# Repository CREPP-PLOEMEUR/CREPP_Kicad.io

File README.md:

# Organisation de la bibliothèque

# Installation d'une bibliothèque via le PCM de KiCad

Ce tutoriel explique comment installer une bibliothèque à partir d'un fichier JSON via le Plugin and Content Manager (PCM) de KiCad.

## Pré-requis

- Avoir installé **KiCad 8** ou une version compatible avec le PCM.
- Disposer de l'adresse du fichier JSON de la bibliothèque :  
  `https://raw.githubusercontent.com/CREPP-PLOEMEUR/CREPP_Kicad.io/refs/heads/main/repository.json`

---

## Étape 1 : Ouvrir le Plugin and Content Manager (PCM)

1. Lancez **KiCad**.
2. Dans le menu principal, cliquez sur **Preferences** > **Manage Plugins**.

---

## Étape 2 : Ajouter un dépôt personnalisé

1. Dans la fenêtre du PCM, cliquez sur l'onglet **Gérer**.

2. Cliquez sur le bouton **Add** pour ajouter un nouveau dépôt.

---

## Étape 3 : Saisir l'URL du dépôt

1. Collez l'adresse suivante dans le champ dédié :  
   `https://raw.githubusercontent.com/CREPP-PLOEMEUR/CREPP_Kicad.io/refs/heads/main/repository.json`
2. Cliquez sur **OK** pour valider.

3. Puis faire **Enregistrer**

---

## Étape 4 : Mettre à jour les bibliothèques

1. Sélectionnez la bibliothèque **Kicad_repository** dans la liste déroulante

2. Cliquez sur le bouton **Plugins** puis **Installer**

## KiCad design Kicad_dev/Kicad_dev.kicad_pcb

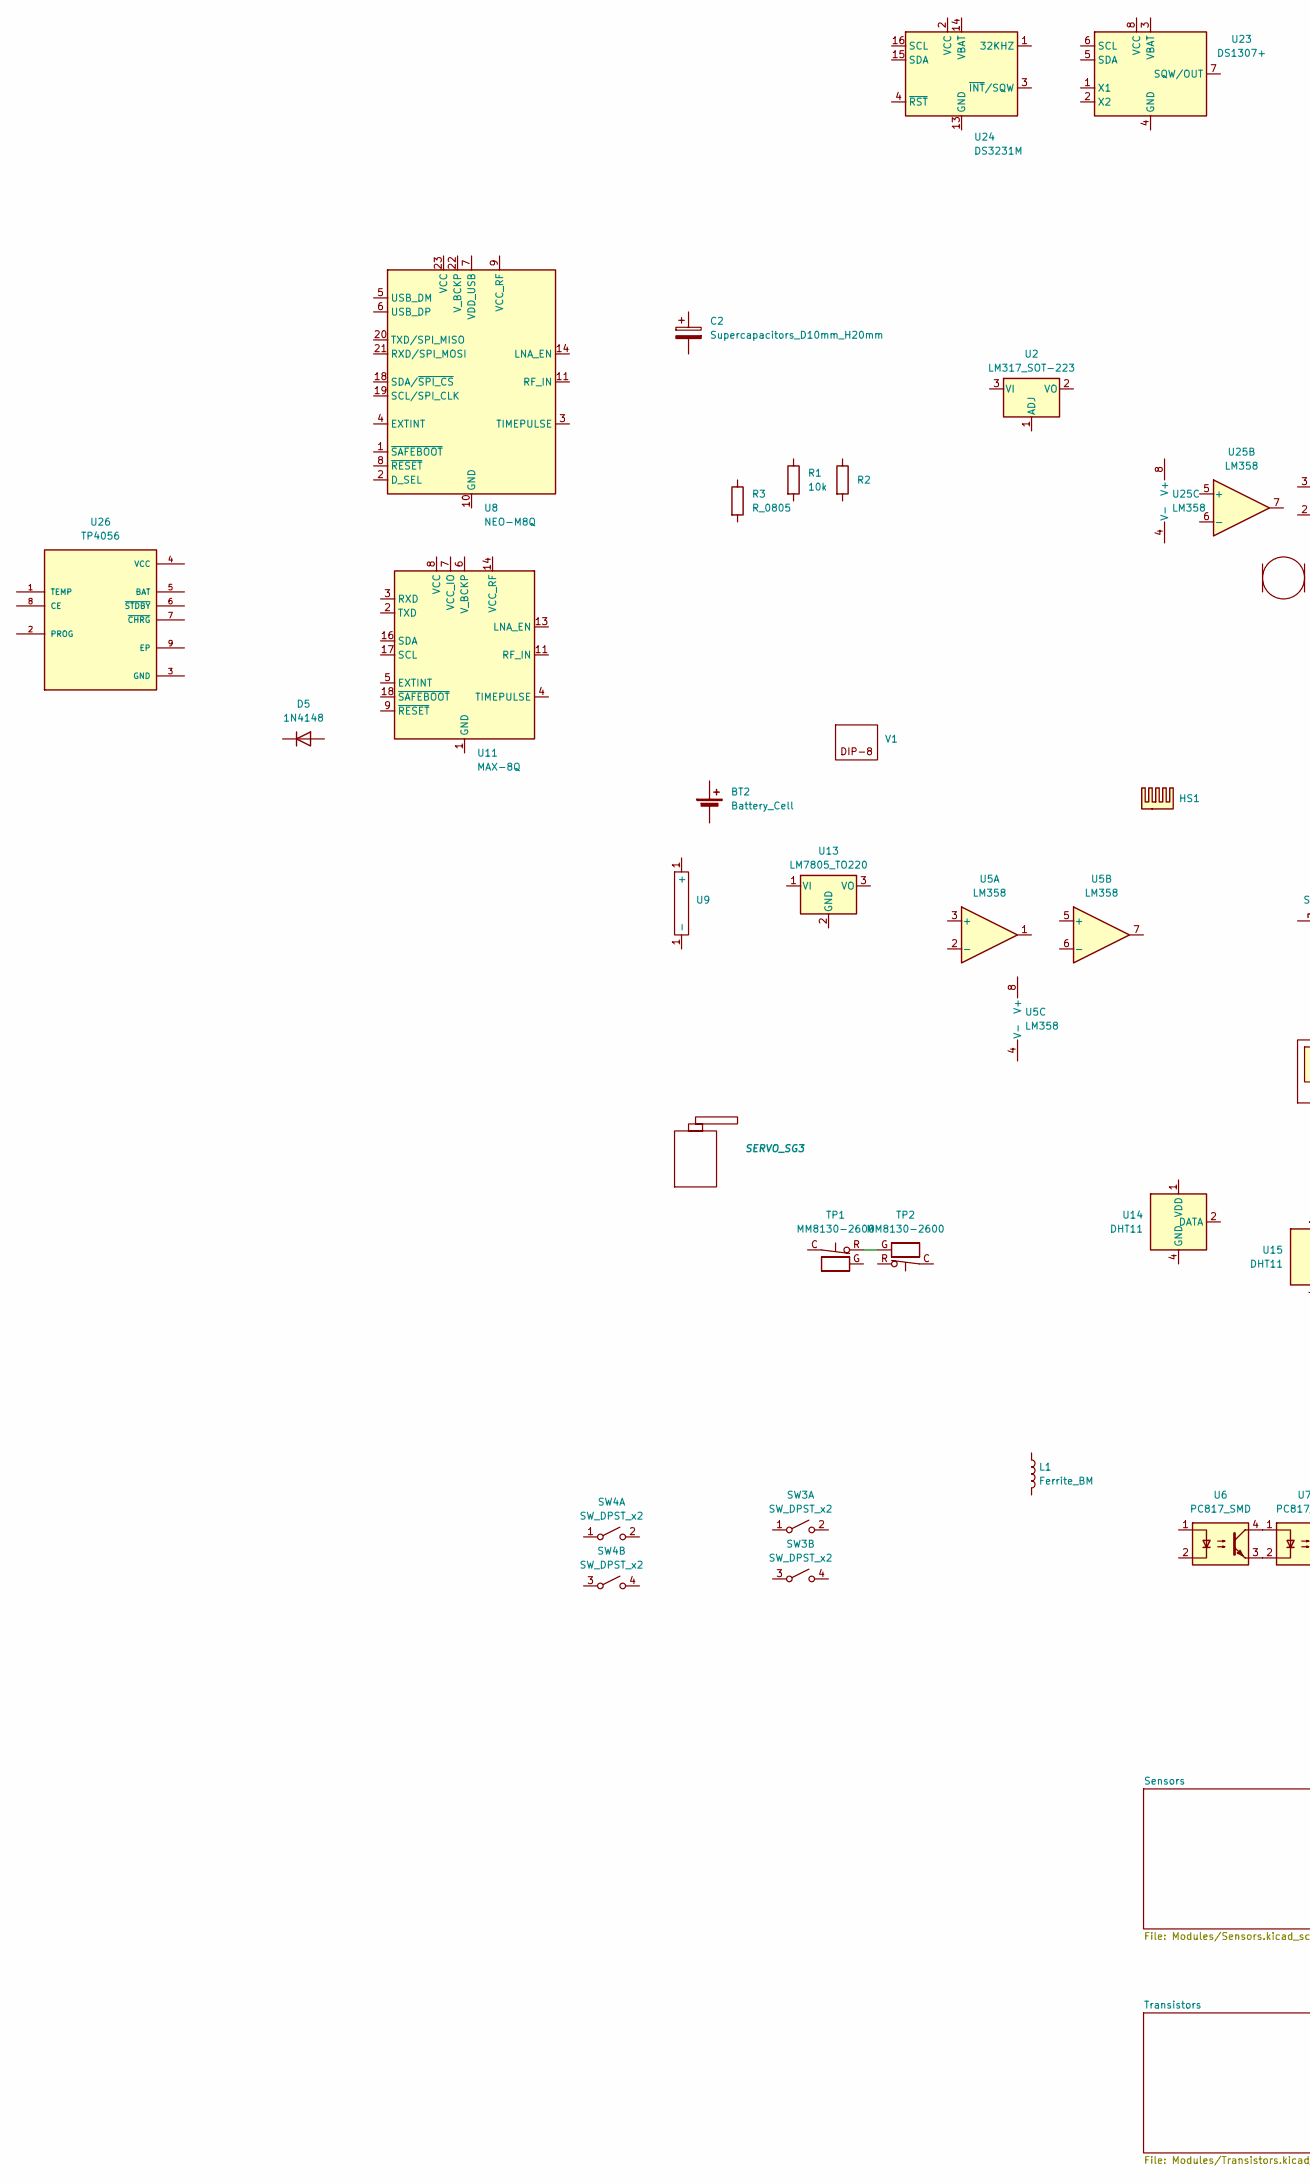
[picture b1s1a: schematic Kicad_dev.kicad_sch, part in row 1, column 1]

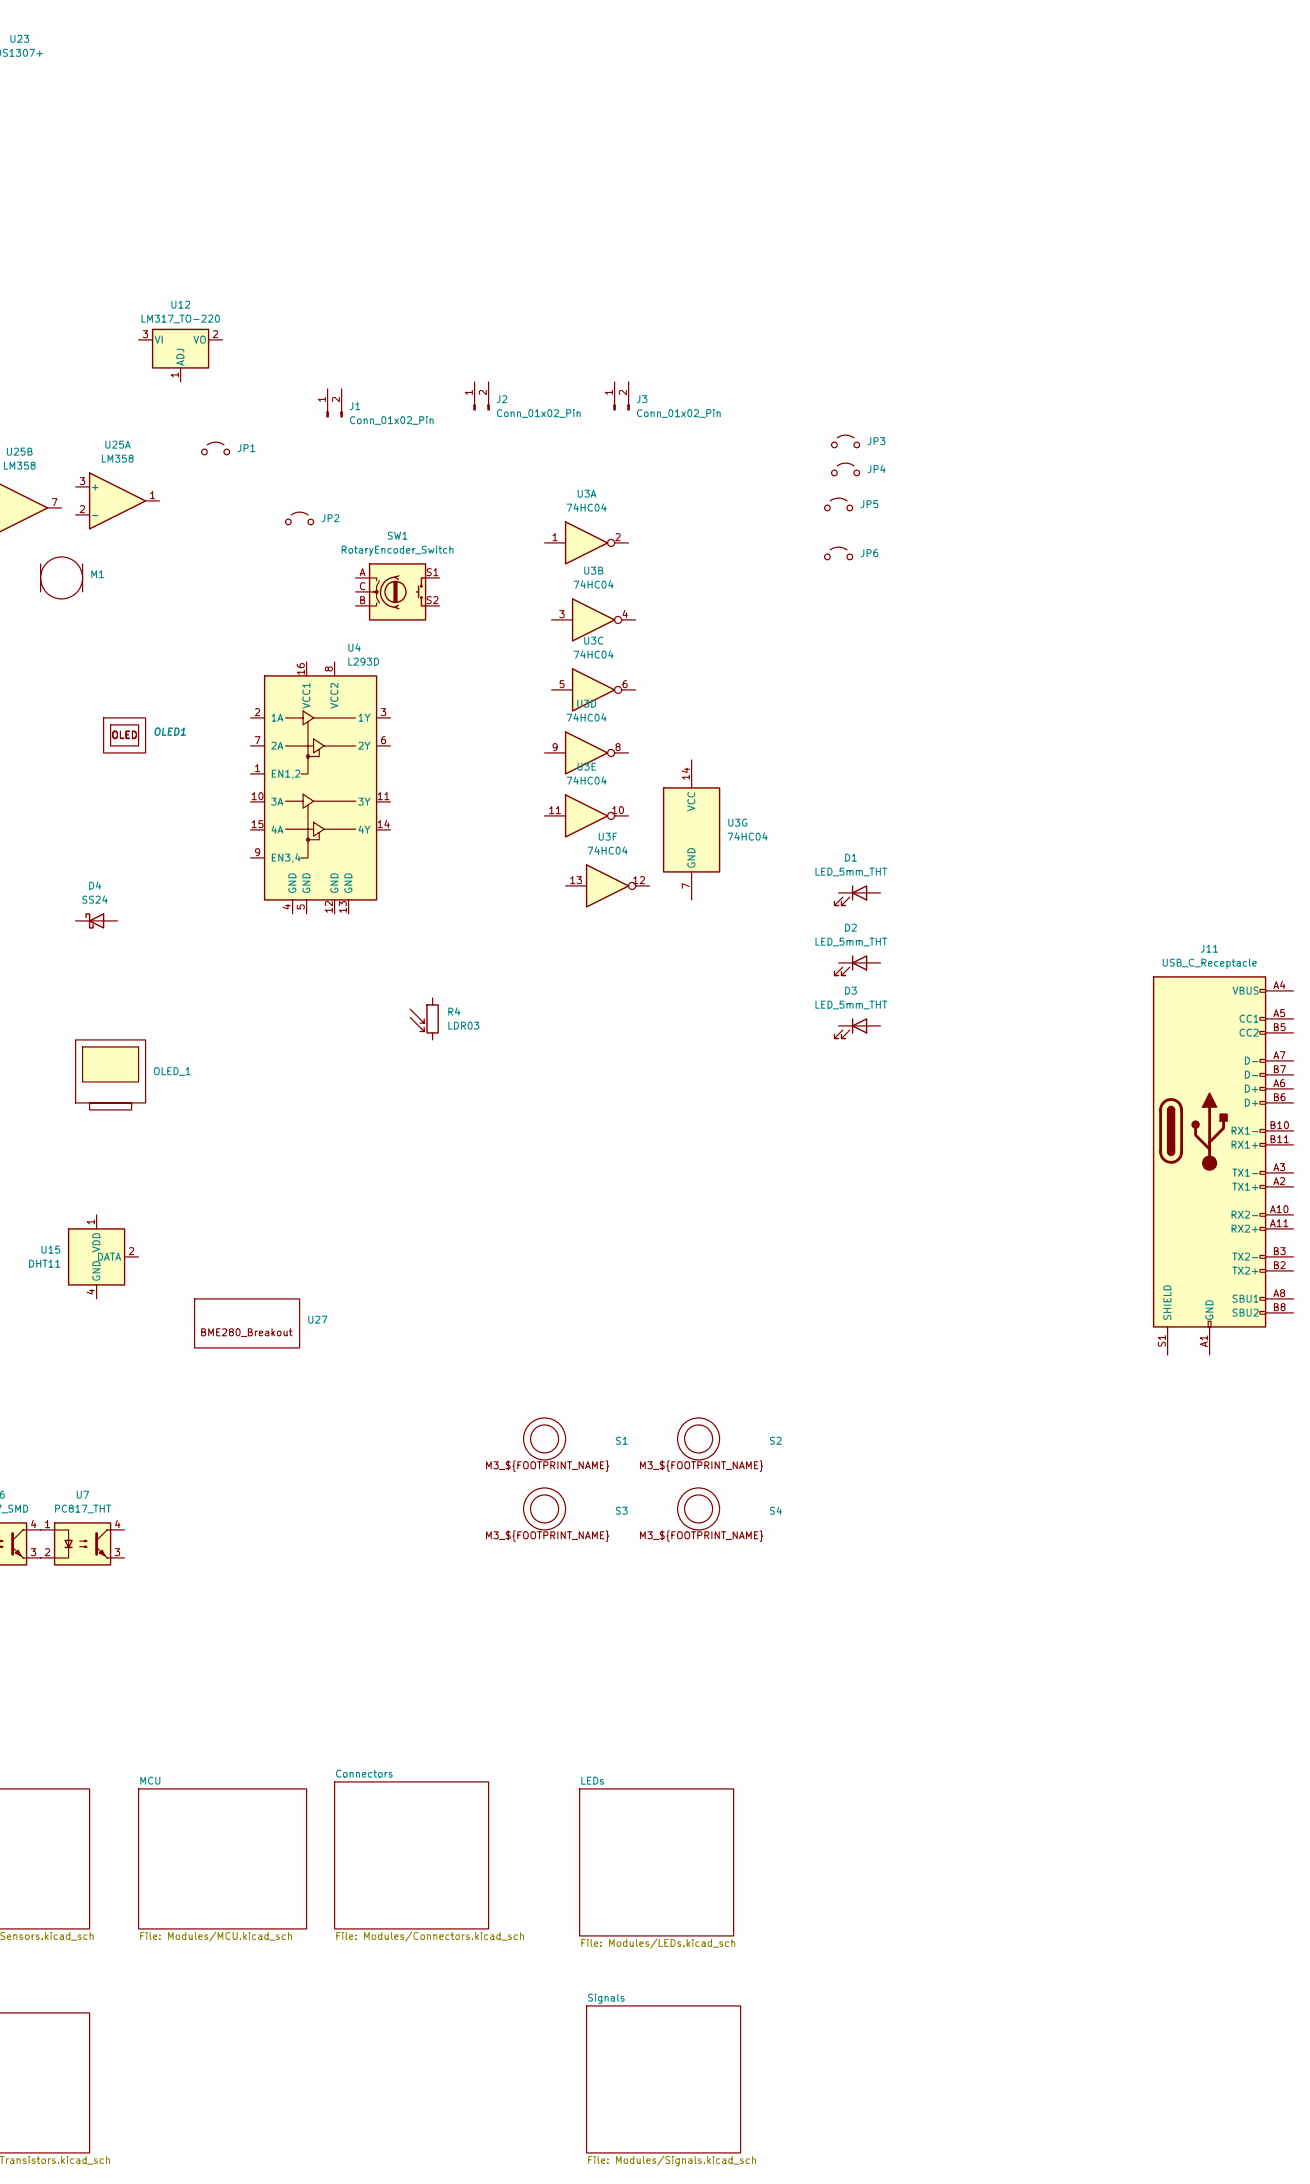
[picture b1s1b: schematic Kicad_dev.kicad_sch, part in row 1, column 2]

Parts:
BT2: Battery_Cell; MPD_BC501SM-TR
C2: Supercapacitors_D10mm_H20mm; C_Radial_D10.0mm_H20.0mm_P5.00mm
D1: LED_5mm_THT; LED_0603_1608Metric
D2: LED_5mm_THT; LED_D5.0mm
D3: LED_5mm_THT; LED_0805_2012Metric
D4: SS24; D_SMA
D5: 1N4148; D_DO-35_SOD27_P7.62mm_Horizontal
HS1: Heatsink [CREPP]; HeastSink_MOSFET_15mm_10mm_20mm
J1, J2, J3: Conn_01x02_Pin; PinHeader_1x02_P2.54mm_Vertical
J11: USB_C_Receptacle; USB_C_Receptacle_GCT_USB4085
JP1, JP4: Jumper_2.54mm_blue
JP2, JP5: Jumper_2.54mm_green
JP3: Jumper_2.54mm_black
JP6: Jumper_2.54mm_red
L1: Ferrite_BM; L_0603_1608Metric
M1: (no value)
OLED1: SSD1306_OLED_Display_VIRTUAL_128_64
OLED_1: SSD1306_OLED_0.96_PCB
R1: 10k; R_Axial_DIN0309_L9.0mm_D3.2mm_P12.70mm_Horizontal
R2: 10k; R_Axial_DIN0207_L6.3mm_D2.5mm_P7.62mm_Horizontal
R3: R_0805; R_0805_2012Metric
R4: LDR03; R_LDR_7x6mm_P5.1mm_Vertical
S1, S2, S3, S4: Spacer_M3_MF_05mm
SERVO_SG3: SG90_Servo
SW1: RotaryEncoder_Switch; RotaryEncoder
SW3: SW_DPST_x2; SW_SPST_PTS645
SW4: SW_DPST_x2; SW_PUSH_6mm_H4.3mm
TP1, TP2: MM8130-2600
U2: LM317_SOT-223; SOT-223-3_TabPin2
U3: 74HC04; DIP-14_W7.62mm_Socket
U4: L293D; DIP-16_W7.62mm_Socket
U5: LM358; DIP-8_W7.62mm_Socket
U6: PC817_SMD; SMDIP-4_W9.53mm
U7: PC817_THT; DIP-4_W7.62mm
U8: NEO-M8Q; ublox_NEO
U9: BK-18650
U11: MAX-8Q; ublox_MAX
U12: LM317_TO-220; TO-220-3_Vertical
U13: LM7805_TO220; TO-220-3_Vertical
U14, U15: DHT11; Aosong_DHT11_5.5x12.0_P2.54mm
U23: DS1307+; DIP-8_W7.62mm_Socket
U24: DS3231M; SOIC-16W_7.5x10.3mm_P1.27mm
U25: LM358; SOIC-8_3.9x4.9mm_P1.27mm
U26: TP4056; SOP127P600X175-9N
U27: BME280_Breakout
V1: DIP-8_W7.62mm

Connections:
unnamed: J11.A1 (GND), J11.A12 (GND), J11.B1 (GND), J11.B12 (GND)
unnamed: J11.A4 (VBUS), J11.A9 (VBUS), J11.B4 (VBUS), J11.B9 (VBUS)
unnamed: TP1.R, TP2.G
unnamed: U6.3, U7.2
unnamed: U6.4, U7.1
unnamed: U8.10 (GND), U8.12 (GND), U8.13 (GND), U8.24 (GND)
unnamed: U11.1 (GND), U11.10 (GND), U11.12 (GND)
unnamed: U24.5 (GND), U24.6 (GND), U24.7 (GND), U24.8 (GND), U24.9 (GND), U24.10 (GND), U24.11 (GND), U24.12 (GND), U24.13 (GND)

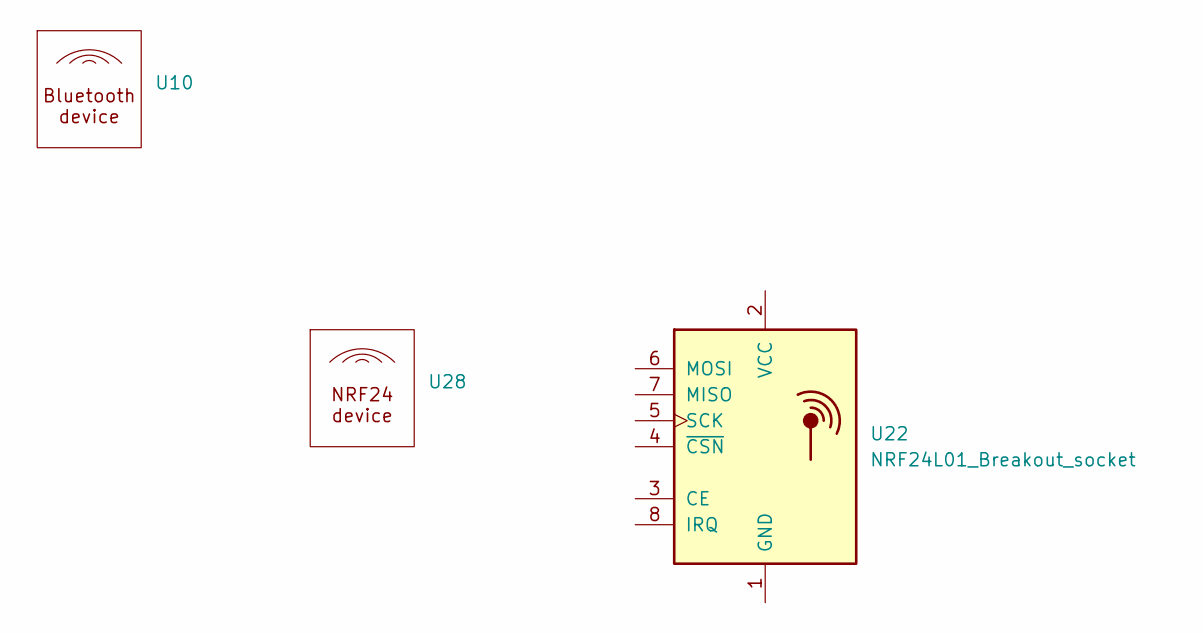
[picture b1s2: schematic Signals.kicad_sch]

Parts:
U10, U28: (no value)
U22: NRF24L01_Breakout_socket; nRF24L01_Breakout

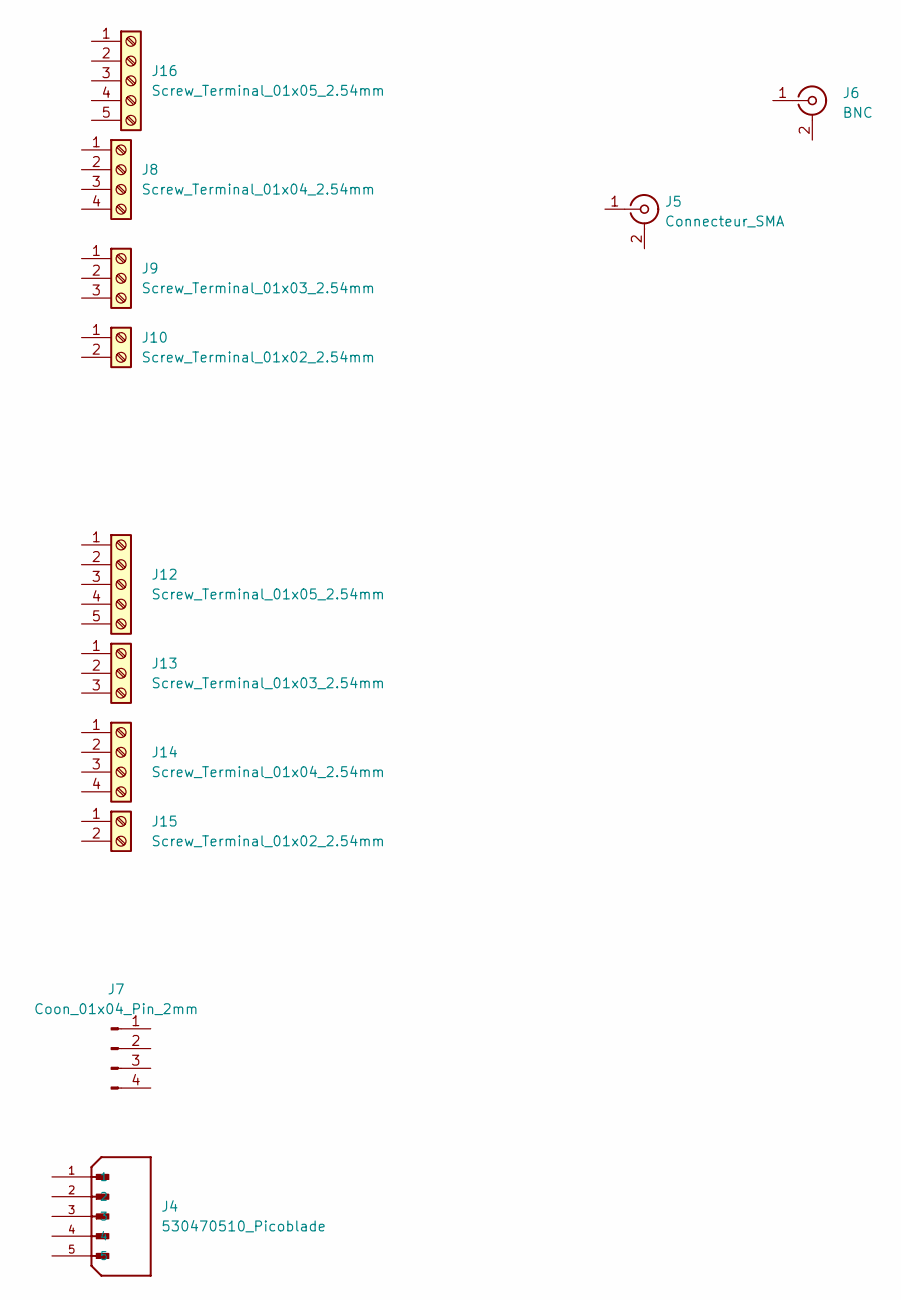
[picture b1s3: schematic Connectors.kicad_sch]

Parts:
J4: 530470510_Picoblade; MOLEX_530470510; PARTREV A
J5: Connecteur_SMA; SMA_Amphenol_132289_EdgeMount
J6: BNC; BNC_Amphenol_B6252HB-NPP3G-50_Horizontal
J7: Coon_01x04_Pin_2mm; JST_PH_B4B-PH-K_1x04_P2.00mm_Vertical
J8: Screw_Terminal_01x04_2.54mm; TerminalBlock_Phoenix_MKDS-1,5-4-5.08_1x04_P5.08mm_Horizont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
J9: Screw_Terminal_01x03_2.54mm; TerminalBlock_Phoenix_MKDS-1,5-3-5.08_1x03_P5.08mm_Horizont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
J10: Screw_Terminal_01x02_2.54mm; TerminalBlock_Phoenix_MKDS-1,5-2-5.08_1x02_P5.08mm_Horizont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
J12: Screw_Terminal_01x05_2.54mm; TerminalBlock_Phoenix_MPT-0,5-5-2.54_1x05_P2.54mm_Horizontal
J13: Screw_Terminal_01x03_2.54mm; TerminalBlock_Phoenix_MPT-0,5-3-2.54_1x03_P2.54mm_Horizontal
J14: Screw_Terminal_01x04_2.54mm; TerminalBlock_Phoenix_MPT-0,5-4-2.54_1x04_P2.54mm_Horizontal
J15: Screw_Terminal_01x02_2.54mm; TerminalBlock_Phoenix_MPT-0,5-2-2.54_1x02_P2.54mm_Horizontal
J16: Screw_Terminal_01x05_2.54mm; TerminalBlock_Phoenix_MKDS-1,5-5-5.08_1x05_P5.08mm_Horizont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

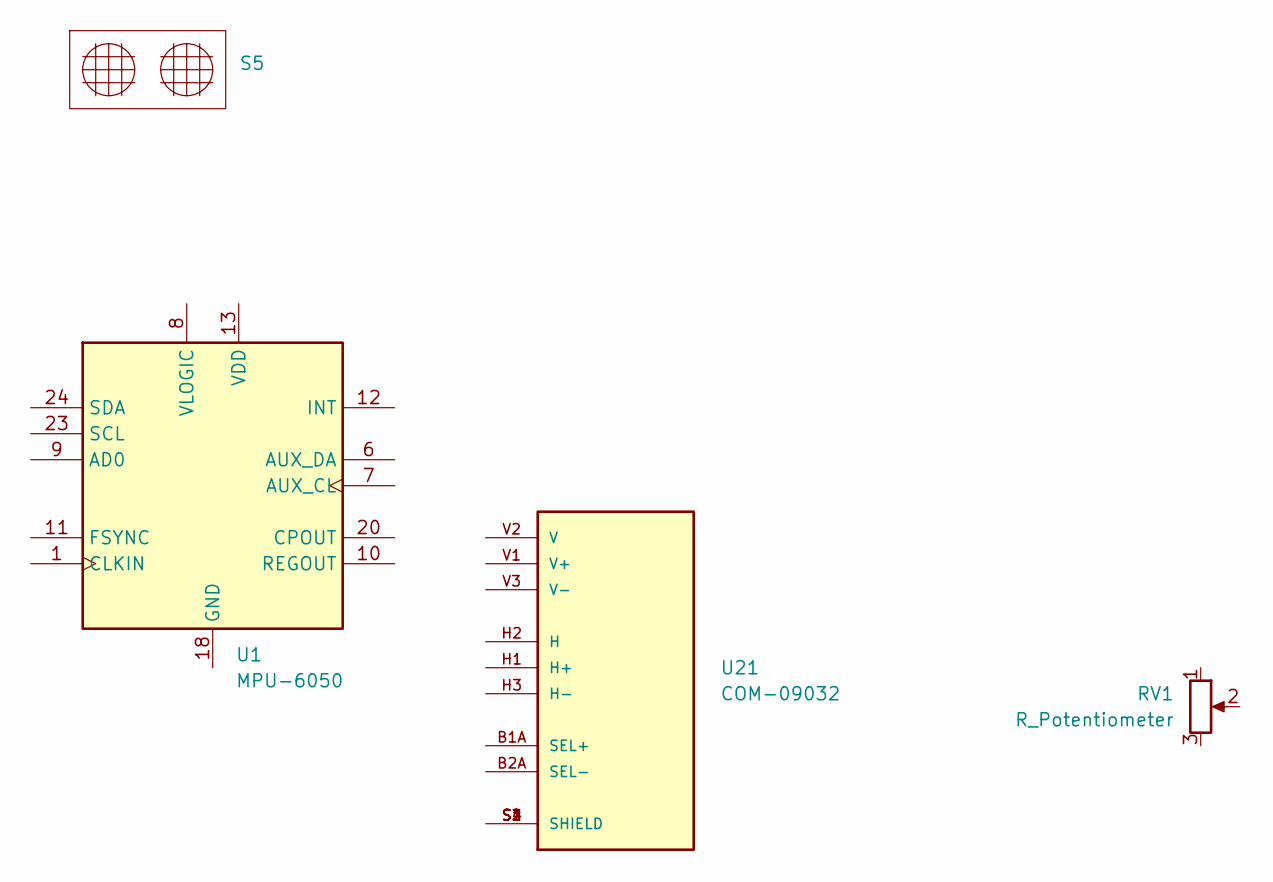
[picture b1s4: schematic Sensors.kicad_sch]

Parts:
RV1: R_Potentiometer; Potentiometer_Alps_RK09Y11_Single_Horizontal
S5: HC-SR04
U1: MPU-6050; InvenSense_QFN-24_4x4mm_P0.5mm
U21: COM-09032; XDCR_COM-09032; PARTREV N/A

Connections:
unnamed: U21.S1 (SHIELD), U21.S2 (SHIELD), U21.S3 (SHIELD), U21.S4 (SHIELD)

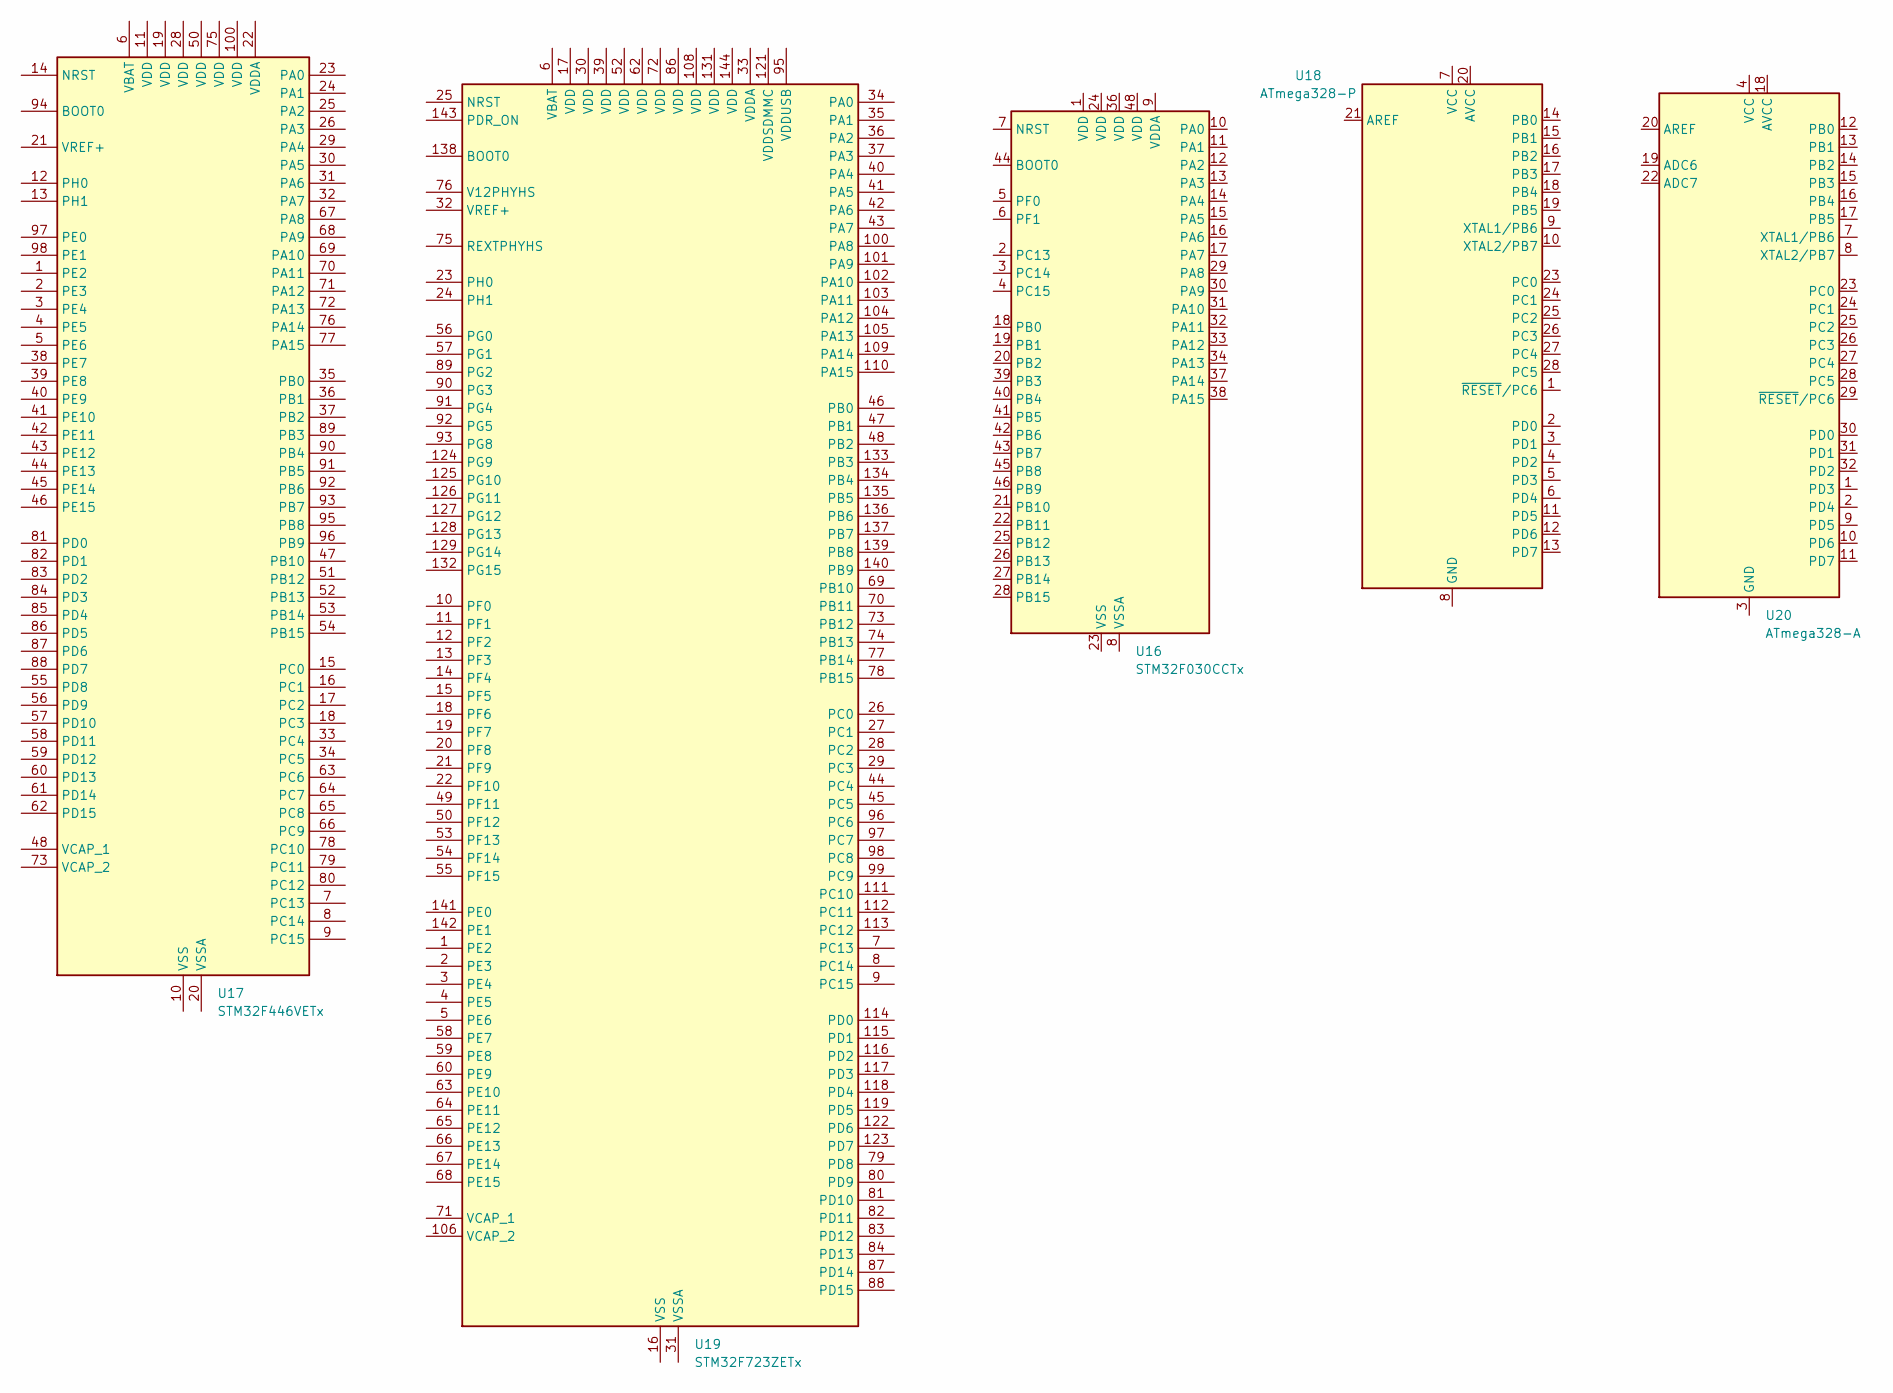
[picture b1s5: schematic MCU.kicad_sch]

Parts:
U16: STM32F030CCTx; LQFP-48_7x7mm_P0.5mm
U17: STM32F446VETx; LQFP-100_14x14mm_P0.5mm
U18: ATmega328-P; DIP-28_W7.62mm
U19: STM32F723ZETx; LQFP-144_20x20mm_P0.5mm
U20: ATmega328-A; TQFP-32_7x7mm_P0.8mm

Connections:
unnamed: U16.23 (VSS), U16.35 (VSS), U16.47 (VSS)
unnamed: U17.10 (VSS), U17.27 (VSS), U17.49 (VSS), U17.74 (VSS), U17.99 (VSS)
unnamed: U18.8 (GND), U18.22 (GND)
unnamed: U19.16 (VSS), U19.38 (VSS), U19.51 (VSS), U19.61 (VSS), U19.85 (VSS), U19.94 (VSS), U19.107 (VSS), U19.120 (VSS), U19.130 (VSS)
unnamed: U20.3 (GND), U20.5 (GND), U20.21 (GND)
unnamed: U20.4 (VCC), U20.6 (VCC)

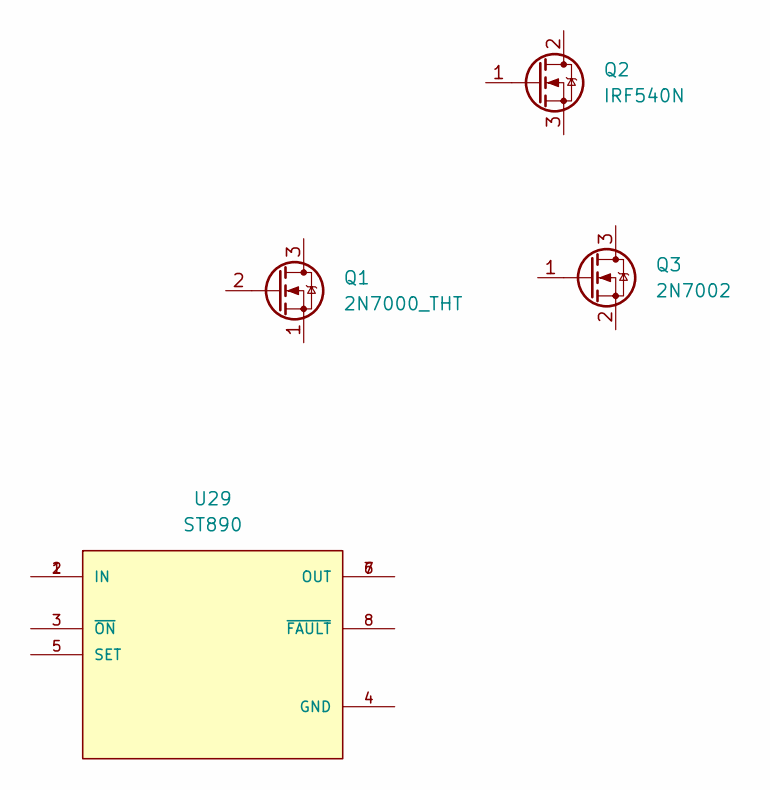
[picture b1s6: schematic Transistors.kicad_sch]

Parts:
Q1: 2N7000_THT; TO-92_Inline
Q2: IRF540N; TO-220-3_Vertical
Q3: 2N7002; SOT-23
U29: ST890; PARTREV 10

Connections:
unnamed: U29.1 (IN), U29.2 (IN)
unnamed: U29.6 (OUT), U29.7 (OUT)

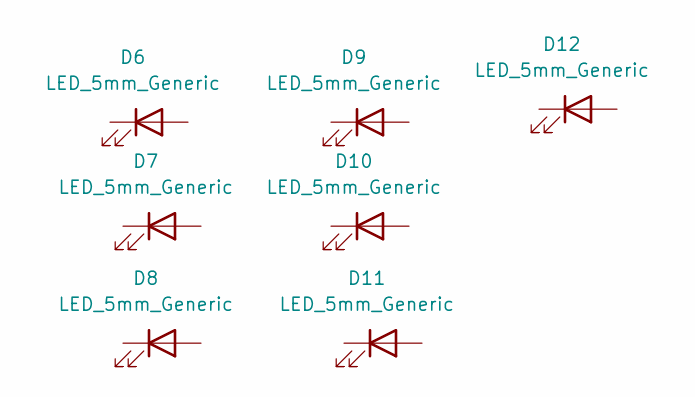
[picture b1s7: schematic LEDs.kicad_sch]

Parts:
D6: LED_5mm_Generic; LED_D5.0mm_Blue
D7: LED_5mm_Generic; LED_D5.0mm_Green
D8: LED_5mm_Generic; LED_D5.0mm_Orange
D9: LED_5mm_Generic; LED_D5.0mm_Purple
D10: LED_5mm_Generic; LED_D5.0mm_Red
D11: LED_5mm_Generic; LED_D5.0mm_White
D12: LED_5mm_Generic; LED_D5.0mm_Yellow

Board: 2 copper layers, 88 parts (0 on the bottom side), 17 nets, no tracks yet.

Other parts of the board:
S5#2: HC-SR04

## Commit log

2024-12-02 Test
2024-12-02 Update tool
2024-12-06 Update of lib
2024-12-09 update lib
2025-01-01 Add drawing file (attempting)
2025-01-01 update lib with generation tools
2025-01-01 upload
2025-01-01 Add symbols
2025-01-01 add lib
2025-01-01 add icon
2025-01-01 add lib version
2025-01-01 Add file
2025-01-05 Add repo of lib Kicad before analyzing...
2025-01-05 Add - (5e4f6eca2dec254def7bfcfd44abc9c64a402f20ab02bed1e3e9a96f647cad6b)
2025-01-05 - (c32471949a067304cb4144130111e2cce4216500af2700b7b9b19f2294e76788)
2025-01-09 - (e3b0c44298fc1c149afbf4c8996fb92427ae41e4649b934ca495991b7852b855)
2025-01-09 restore
2025-01-09 Add - (e3b0c44298fc1c149afbf4c8996fb92427ae41e4649b934ca495991b7852b855)
2025-01-09 Add - (49cfa93f1f5549816a1b8512ae3cd13204bf6c776ec739aeb292c13e334a96dc)
2025-01-18 TEST after new commité
2025-01-18 ADD - (79088ea3c5c0b3900a73a4b08ca3f8c79786b0477343f9c28eaa13bca8400a77)
2025-01-18 ADD - (922ac99b1a6d729701d29990a9a5855193f02730671ecf40d52a617529a50940)
2025-01-18 TEST after new commit
2025-01-18 TEST after new commit - (eea2a385d7bde658bdcfa98affe8a7cbf9c1ec28949d9a6fbb0c5bad26c39ce2)
2025-01-18 Add - (be9e3e141a35f29320ea2a8d915ac20d7eab441ba76d2e379f0d4dc9706c2059)
2025-01-18 Add - (b0084782d5078a4f694cabc07fe4801196ee21d7b56ade77b9c5fe29a431285b)
2025-01-18 Add - (2336ce0af787beb11383f9e405e50a9fa70a61aa77f1abbf6fc40f0117b1caf9)
2025-01-18 Add - (d28bd325be9e34bb58607fc95e831af932fd1003b757bfae3e66fa5f53f0ec05)
2025-01-20 Update src git
2025-01-20 Update src git - (9da9e5ef98b1046a42052b9141ef9e61d441375bad7d33e9f7f8014bbea5ff20)
2025-01-20 Update src git and link
2025-01-20 Update src git and link - (f07ababd16f1d4357f5e48e15420aa1fcc698d40236abb387f8f44ee15c88708)
2025-01-20 Add OLED PCB mount
2025-01-20 Add OLED PCB mount - (da7f63433467c8894aa3f3270ed5163d3abc7fb2351fb2af8202e9e281b7087b)
2025-01-21 Add OLED PCB mount - (eaeee60e9d60c9f14c34aa8779c09a53a0179d9ecb73a5c2d925396e647d6e47)
2025-01-21 Add OLED PCB mount - (1f0e681fe6f4f537cf181844c1b6c4f57439430e19f2f746a5b5f1a0b7456f62)
2025-02-08 Update - (1e688b2839f43b0108f1f04d0339f95b7d2bef09412adb31825657eca342bfba)
2025-02-08 Update - (ecb5bf4f4227796b1c2942bcf165ec14f6297006718bfb26d70a0cb4508ee822)
2025-02-08 Update - (c98ef3e8d8982d98dbddcbde18990c883e78b43ce68c00ccc912a08f956cdddb)
2025-02-08 Update - (7554bd46c7ec126cc8bfe683cb9c2785b30cf9f940126a0207421f011d9e6d88)
2025-02-08 Update - (ab7eaeea5e781641bd56af095af11f0a19457e42d6d753a01b313be1ac33bcd2)
2025-02-08 Update - (30431b91cdea9446cb5d4a67193b4565dcfa51603bb672422811bb4e04951458)
2025-02-08 Update - (4e3b7aaebfb6fb283afdfe9db8d2cf83d1e0f31cc76046f395521e54ee994bb8)
2025-02-11 - (4e3b7aaebfb6fb283afdfe9db8d2cf83d1e0f31cc76046f395521e54ee994bb8)
2025-02-20 Add - (7c4fd84f9658a72323e4990959139752aa56df1d426c45a6dfaf2142f6b067e0)
2025-02-20 Add - (9d9b188eecfab5e567fa946b0ec4e69f9a1270352ea878e80603ad049681f501)
